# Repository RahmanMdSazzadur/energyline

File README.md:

# EnergyLine

Assembly-line simulation, a virtual fastening cell, n8n workflows, a routed PCB prototype and a standalone Arduino demonstration.

Start with `START_HERE.md` or open `RELEASE_INDEX.html` from the extracted folder. Version 1.1.1 combines all current deliverables in `EnergyLine-v1.1.1-final.zip`.

EnergyLine studies how a five-station mock energy-module assembly line could meet a demand of 240 good units per shift. The model compares staffing, finite buffers, a second manual fixture and selective automation. Process times, failure rates, quality inputs and prices are assumptions. No physical production data is used.

## Access and reuse

- Run the full Python app online: https://energyline-demo.onrender.com/
- Public repository: https://github.com/RahmanMdSazzadur/energyline
- Online project overview: https://rahmanmdsazzadur.github.io/energyline/
- Download the reviewed package: https://github.com/RahmanMdSazzadur/energyline/releases/tag/v1.1.1
- Interactive Arduino demonstration: https://wokwi.com/projects/480261288480719873

The project page serves static documentation, video, drawings and saved circuit results. It does not run the Python app or n8n in the browser. To run the full app, clone this repository, enter its folder, and follow the local setup below. GitHub Actions checks the software tests, Arduino controller core and archive contents; it does not run physical hardware tests.

```sh
git clone https://github.com/RahmanMdSazzadur/energyline.git
cd energyline
python3 src/api/server.py
```

The full Python app is live on Render Free at https://energyline-demo.onrender.com/. Visitors do not need an account or local Python setup. Free hosting sleeps when idle and stores shared, temporary runs. `render.yaml` and `docs/hosting.md` describe deployment and limits. The tagged v1.1.1 ZIP is the reviewed local-prototype release; the main branch also includes the hosted-demo additions.

Original project work is available under the MIT license. See `LICENSE`, `THIRD_PARTY_NOTICES.md` and `CONTRIBUTING.md`.

## Main result

With the faster S2/S3 configuration, four production operators plus one rework operator meet demand in 198 of 200 simulated shifts. The 95% Wilson lower bound is 96.4%. Three production operators cost less per unit but meet demand in 183 of 200 shifts, with an 86.8% lower bound.

Adding a second manual S3 resource at fixed staffing raises output from 163.4 to 200.5 units per shift. S2 then limits the line. The study therefore supports investigating both S2 and S3 rather than buying an S3 machine on the basis of its standalone cycle time.

These results apply to the configured model. Loading, walking, unloading and inspection performance need measured inputs before an equipment decision.

## Run locally

Use Python 3.13.7. The application and tests use the standard library; no pip packages are required.

`python3 src/api/server.py`

Open `http://localhost:8787/portfolio` for the case study, drawings and video. The application also provides the experiment studio at `/`, the S3 cell at `/cell` and the cost comparison at `/costs`. These are local addresses, not public hosting links.

For Docker and n8n setup, see `n8n/README.md`. n8n coordinates experiments and commissioning tests; it does not control physical motion.

## Verify and reproduce

- Tests: `python3 -m unittest discover -s tests -q`
- Regenerate numerical evidence and drawings: `python3 scripts/reproduce.py`
- Optional video rendering: `python3 scripts/build_demo.py` (requires `requirements-media.txt` and ffmpeg).
- Build the source archive: `python3 scripts/package_release.py`

The reviewed version has 103 passing tests and 11 recorded commissioning cases. Six cost configurations each use 200 replications. Separate studies cover staffing, timing variation, failures, quality, parallel S3 resources and the per-unit controller adapter. Seeds, configurations and checksums are saved with the results.

## Project structure

- `src/simulation/`: production flow, operators, buffers, quality and reliability.
- `src/controls/`, `src/equipment_model/`, `src/cell/`: S3 controller, plant and commissioning harness.
- `src/analysis/`: experiment drivers and conversion-cost calculations.
- `configs/`: model and cost inputs.
- `tests/`: reference cases, invariants, fault responses and API checks.
- `cad/`: OpenSCAD concepts, dimensioned SVG drawings and a DXF layout.
- `docs/final_case_study.md`: methods, results and engineering interpretation.
- `docs/engineering_review.md`: review findings and corrections.
- `docs/assumptions_register.md`, `docs/requirements_audit.csv`: input and evidence records.
- `n8n/`: workflow definitions and setup instructions.
- `media/`: two-minute software demonstration and captions.
- `electrical/`: KiCad project, routed Revision A PCB, 3D envelope, ngspice evidence and fabrication files.
- `wokwi/`: Arduino sketch, virtual wiring, tests and saved project URL.
- `docs/release_notes.md`: combined release contents and component boundaries.

## Limits

The cell and line adapter run in software. Cell timings are scaled to an assumed line cycle, and the adapter resets the cell each cycle. Its results are reported separately from the economic study.

Mechanical CAD is conceptual and has not been compiled or qualified for manufacture. The electrical PCB has passed configured KiCad DRC, ERC and schematic parity checks, but has not been manufactured or physically tested. The Wokwi LED controller is a standalone demonstration, not a full port of the virtual S3 controller or a connection to n8n. No measured assembly times, real machine operation, supplier quotations or certified safety functions are claimed. The model omits separate walking/unloading tasks, inspection errors, constrained repair labor, replenishment and shift carryover. Good-unit materials and general overhead are excluded from the reported conversion cost.

Version 1.1.1 is a combined simulation and engineering-prototype release. PCB Revision A and the Wokwi demonstration retain their own validation limits; see `docs/scope_and_validation.md`.

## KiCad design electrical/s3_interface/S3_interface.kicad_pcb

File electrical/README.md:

# S3 bench interface and simulation

This extension models a 5 V bench interface with an LED mock clamp load and two active-low dry-contact inputs. It is not an industrial actuator circuit or a certified safety circuit.

## Open and reproduce

Start the browser KiCad service with `docker compose -f electrical/compose.yaml up -d`, then open http://localhost:3090. The project inside KiCad is `/project/S3_interface.kicad_pro`.

Export the schematic connectivity before rerunning a changed design:

```sh
docker exec energyline-kicad kicad-cli sch export netlist --format kicadxml --output /project/S3_interface.net.xml /project/S3_interface.kicad_sch
docker exec energyline-kicad apk add --no-cache ngspice
python3 electrical/run_simulation.py
```

The ngspice installation is local to the container and must be repeated if it is recreated. The runner checks the exported net connections, derives component values from that export, and adds explicit simulation sources and generic device models. It runs ngspice externally rather than through KiCad's integrated simulator.

## Results

The 40 ms transient run produced 20,201 samples and passed 12 functional checks. Enabled LED current was 4.149 mA, transistor collector voltage was 0.049 V, and input 10–90% rise time was 219.83 microseconds. Removing the permit inhibited LED current while the command remained high.

Open `s3_interface/simulation/report.html`, or http://localhost:8787/circuit-simulation while the main application is running. Raw results, the SPICE deck, engine log, CSV samples and SVG waveforms are in `s3_interface/simulation/`.

## Model limits

The NPN and LED models are generic; the BC547B is not calibrated against manufacturer measurements. Controller outputs and contacts are ideal sources/switches. The fuse is represented by 1 ohm and does not trip. Input thresholds of 1.5/3.5 V are assumed. Mechanical bounce, EMC, ESD, tolerance and thermal effects are not analyzed. The 100 microsecond RC time constant is not a complete mechanical debounce solution. These results demonstrate modeled behavior, not tested hardware performance.

The combined EnergyLine v1.1.0 release includes this electrical extension alongside the software and Wokwi files.

## Routed PCB Revision A

The current board is `s3_interface/S3_interface.kicad_pcb`, with assembly details in `s3_interface/ASSEMBLY.md`. It uses standard library footprints, four M3 mounting holes and complete two-layer routing. DRC, schematic parity and ERC reports are saved alongside it. Fabrication exports are in `s3_interface/fabrication/rev_A/`. The superseded placement draft is excluded from the combined release.

To regenerate after confirming component choices, copy `electrical/pcb_components.json` to `electrical/s3_interface/pcb_components.json`, regenerate the schematic and XML netlist, then run `docker exec energyline-kicad python3 /project/build_rev_a.py`. Rerun DRC, ERC and simulation after any design change, and regenerate manufacturing files from the checked board. Native KiCad footprints are taken from the installed KiCad 10.0.3 library.

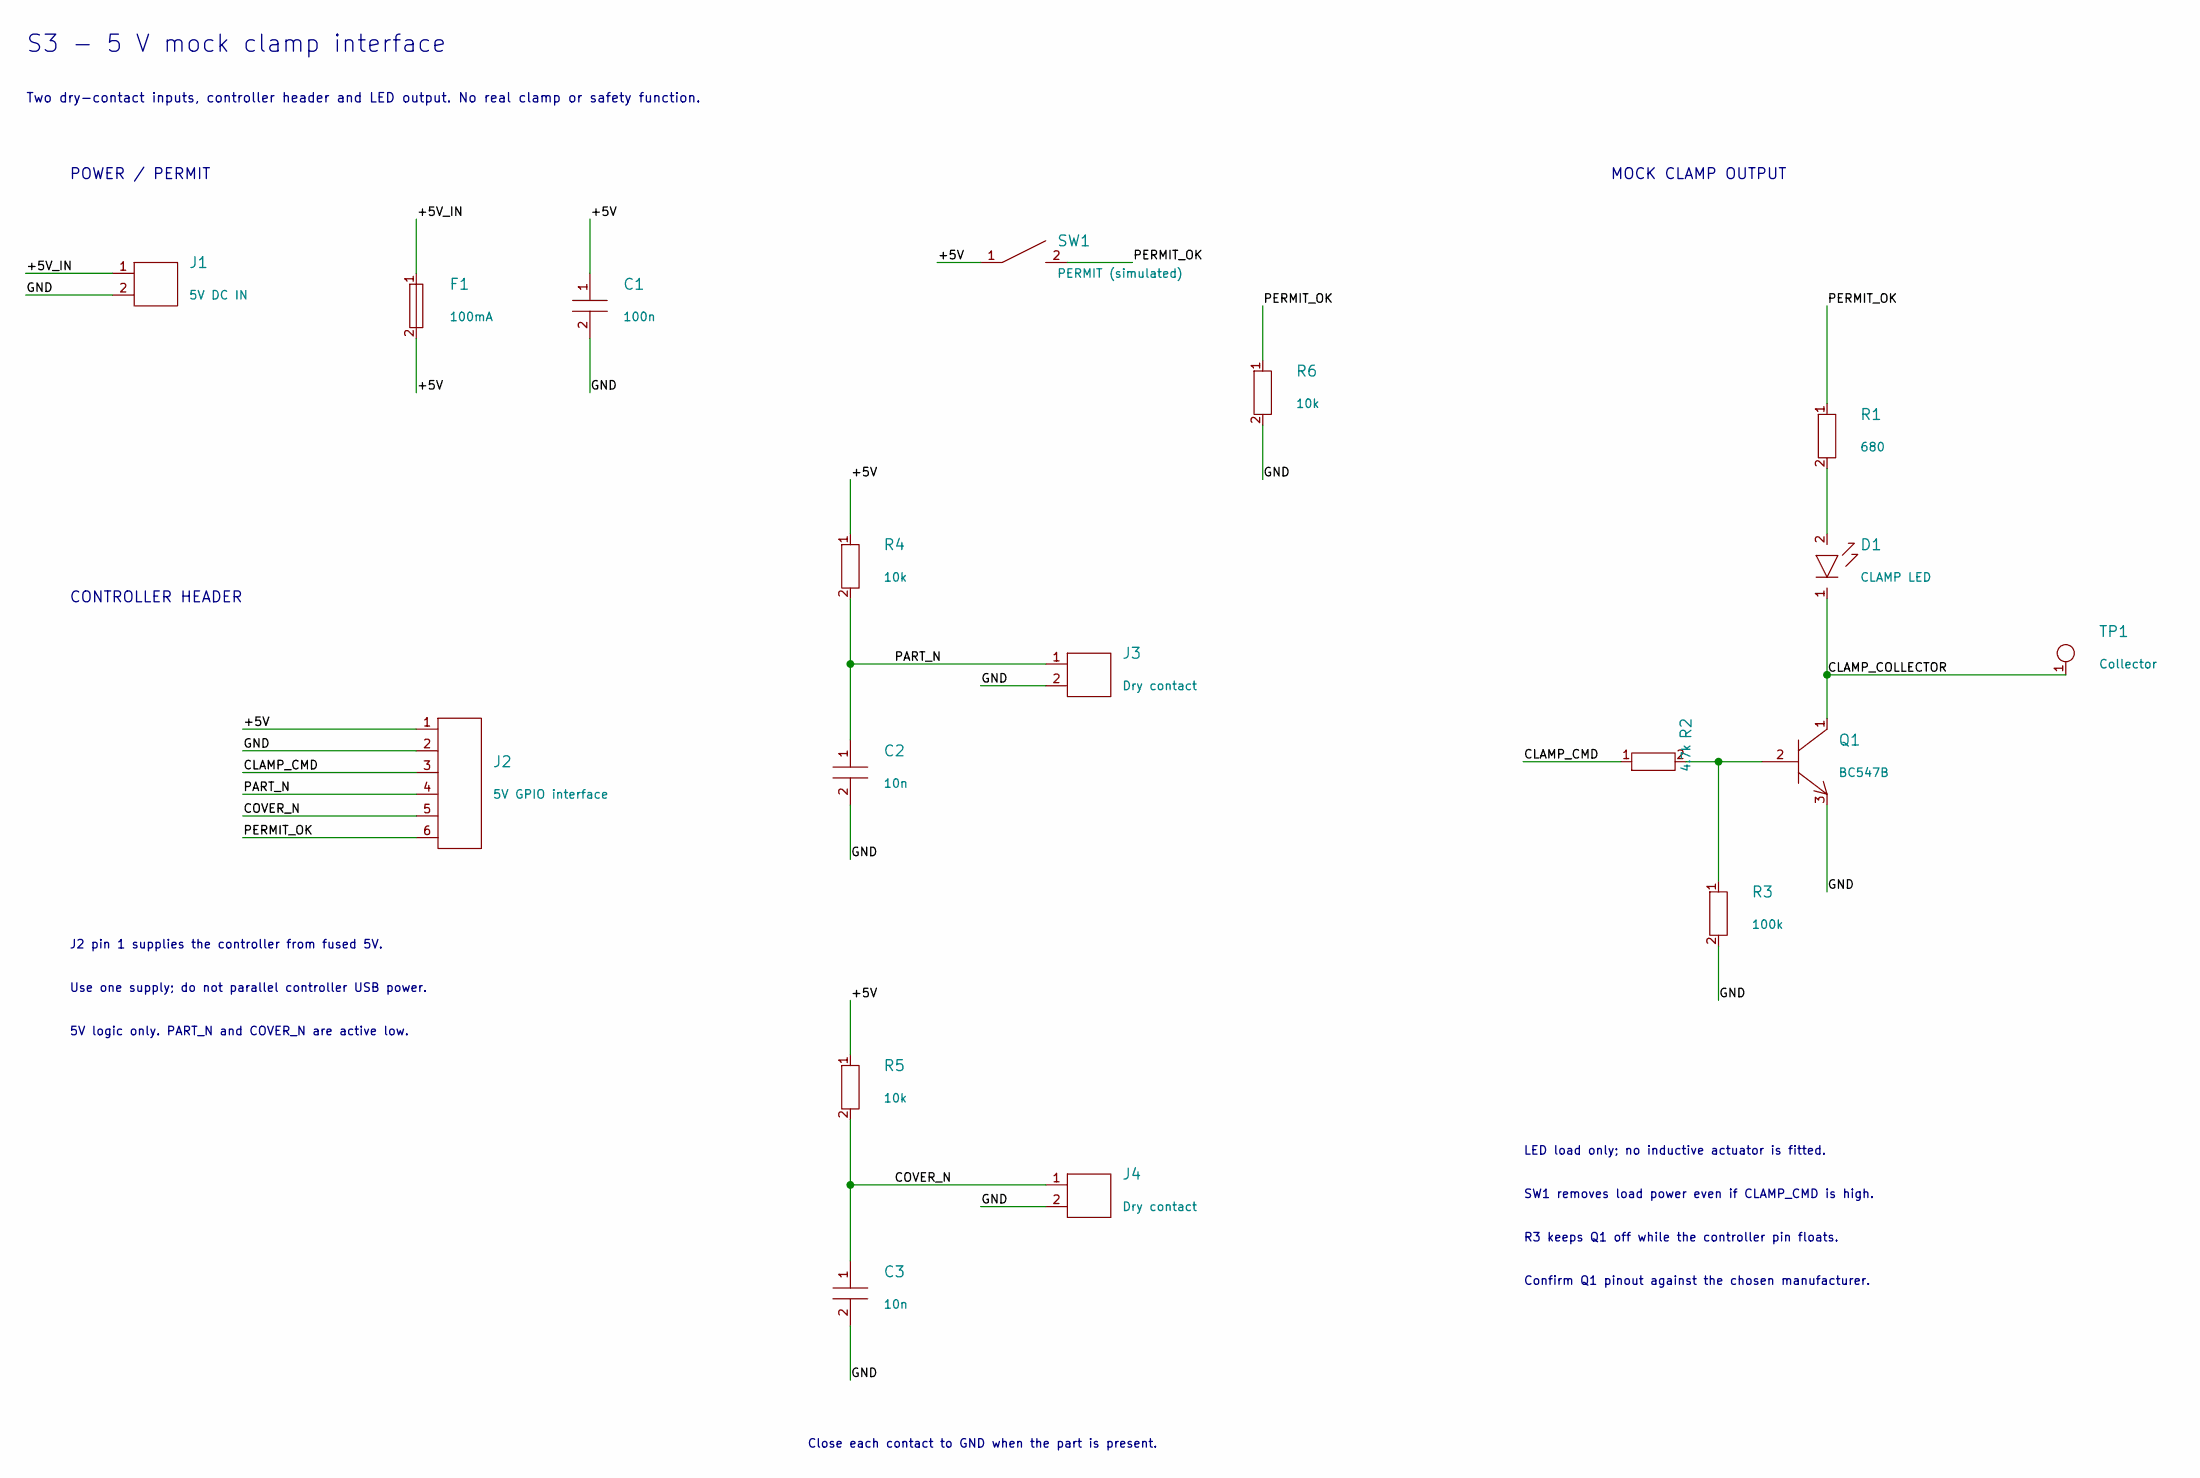
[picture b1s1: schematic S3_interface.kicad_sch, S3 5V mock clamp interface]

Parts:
C1: 100n; C_Disc_D5.0mm_W2.5mm_P5.00mm
C2, C3: 10n; C_Disc_D5.0mm_W2.5mm_P5.00mm
D1: CLAMP LED; LED_D3.0mm
F1: 100mA; Fuse_Littelfuse_372_D8.50mm
J1: 5V DC IN; PinHeader_1x02_P2.54mm_Vertical
J2: 5V GPIO interface; PinHeader_1x06_P2.54mm_Vertical
J3, J4: Dry contact; PinHeader_1x02_P2.54mm_Vertical
Q1: BC547B; TO-92_Inline_Wide
R1: 680; R_Axial_DIN0207_L6.3mm_D2.5mm_P7.62mm_Horizontal
R2: 4.7k; R_Axial_DIN0207_L6.3mm_D2.5mm_P7.62mm_Horizontal
R3: 100k; R_Axial_DIN0207_L6.3mm_D2.5mm_P7.62mm_Horizontal
R4, R5, R6: 10k; R_Axial_DIN0207_L6.3mm_D2.5mm_P7.62mm_Horizontal
SW1: PERMIT (simulated); PinHeader_1x02_P2.54mm_Vertical
TP1: Collector; TestPoint_THTPad_D2.0mm_Drill1.0mm

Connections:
/+5V: C1.1, F1.2, J2.1, R4.1, R5.1, SW1.1
/+5V_IN: F1.1, J1.1
/CLAMP_CMD: J2.3, R2.1
/CLAMP_COLLECTOR: D1.1 (K), Q1.1 (C), TP1.1
/COVER_N: C3.1, J2.5, J4.1, R5.2
/GND: C1.2, C2.2, C3.2, J1.2, J2.2, J3.2, J4.2, Q1.3 (E), R3.2, R6.2
/PART_N: C2.1, J2.4, J3.1, R4.2
/PERMIT_OK: J2.6, R1.1, R6.1, SW1.2
unnamed: D1.2 (A), R1.2
unnamed: Q1.2 (B), R2.2, R3.1

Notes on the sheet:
S3 - 5 V mock clamp interface
Two dry-contact inputs, controller header and LED output. No real clamp or safety function.
POWER / PERMIT
CONTROLLER HEADER
J2 pin 1 supplies the controller from fused 5V.
Use one supply; do not parallel controller USB power.
5V logic only. PART_N and COVER_N are active low.
Close each contact to GND when the part is present.
MOCK CLAMP OUTPUT
LED load only; no inductive actuator is fitted.
SW1 removes load power even if CLAMP_CMD is high.
R3 keeps Q1 off while the controller pin floats.
Confirm Q1 pinout against the chosen manufacturer.

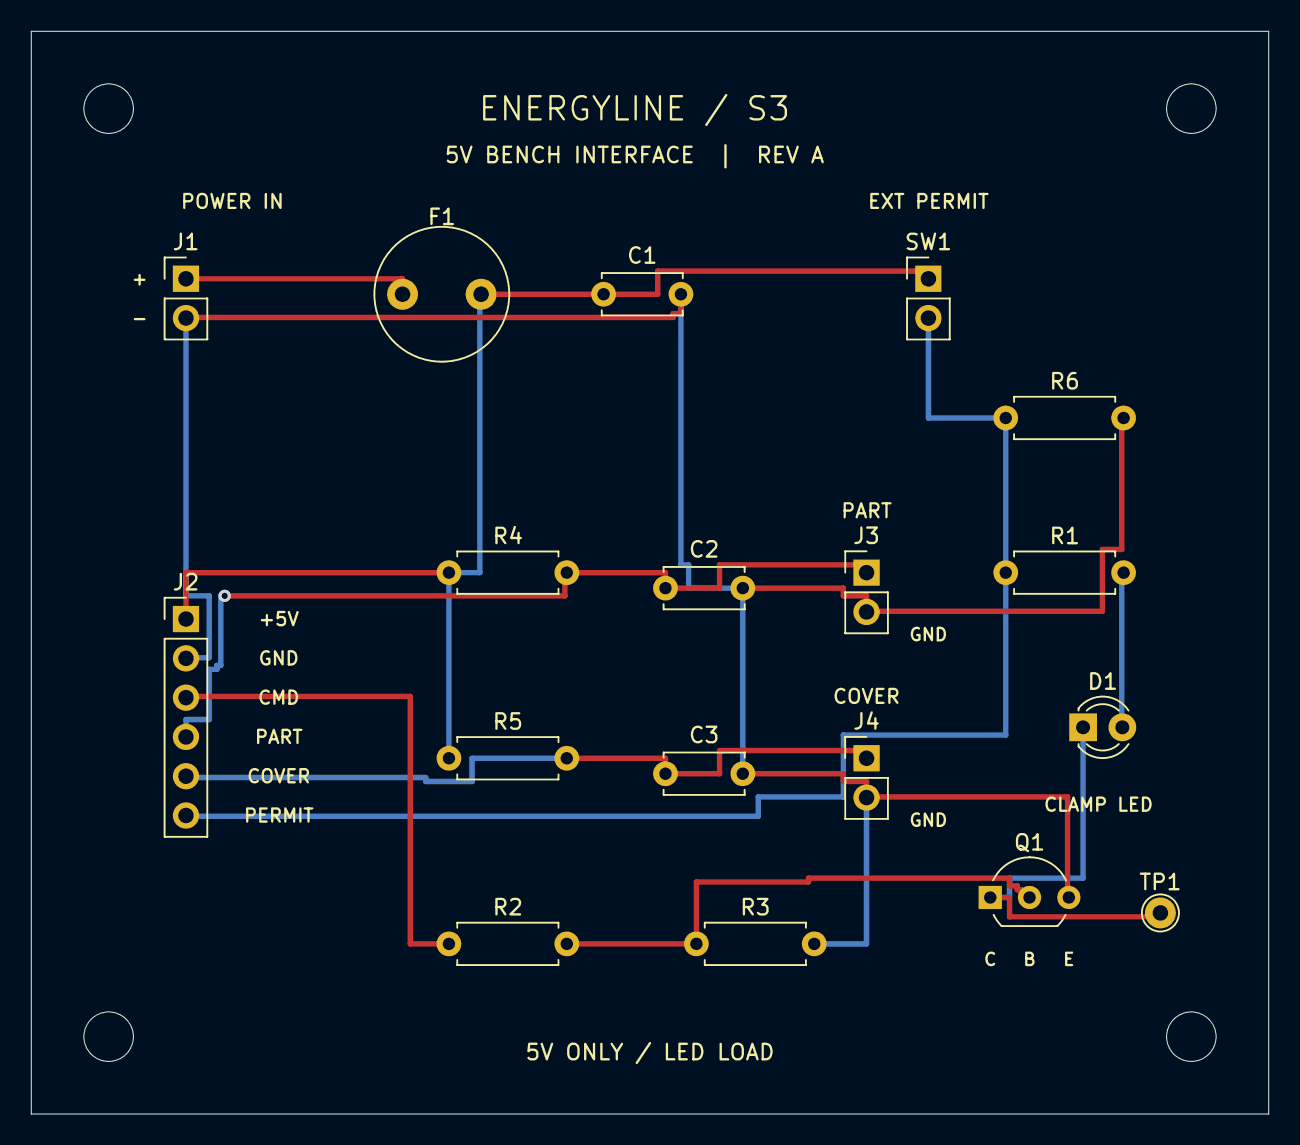
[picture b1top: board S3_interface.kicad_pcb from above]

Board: 2 copper layers, 80.0 x 70.0 mm, 22 parts (0 on the bottom side), 10 nets.

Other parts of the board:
H1, H2, H3, H4: M3; MountingHole_3.2mm_M3

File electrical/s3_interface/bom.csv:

reference,value,symbol,x_mm,y_mm,angle
J1,5V DC IN,Conn_2,30.48,43.18,0
F1,100mA,Fuse,60.96,45.72,0
C1,100n,C,81.28,45.72,0
SW1,PERMIT (simulated),Switch_SPST,132.08,40.64,0
R6,10k,R,160.02,55.88,0
J2,5V GPIO interface,Conn_6,66.04,101.6,0
R4,10k,R,111.76,76.2,0
J3,Dry contact,Conn_2,139.7,88.9,0
C2,10n,C,111.76,100.33,0
R5,10k,R,111.76,137.16,0
J4,Dry contact,Conn_2,139.7,149.86,0
C3,10n,C,111.76,161.29,0
R1,680,R,226.06,60.96,0
D1,CLAMP LED,LED,226.06,76.2,0
Q1,BC547B,NPN_CBE,223.52,99.06,0
R2,4.7k,R,205.74,99.06,90
R3,100k,R,213.36,116.84,0
TP1,Collector,TestPoint,254,86.36,0

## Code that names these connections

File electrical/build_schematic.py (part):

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
    d.text('CONTROLLER HEADER',20.32,80.01)
    j2=d.place('Conn_6','J2','5V GPIO interface',66.04,101.6)
    mapping=['+5V','GND','CLAMP_CMD','PART_N','COVER_N','PERMIT_OK']
    for number,name in enumerate(mapping,1):d.stub(j2[str(number)],(40.64,j2[str(number)][1]),name)
    d.text('J2 pin 1 supplies the controller from fused 5V.',20.32,120.65,1.0)
    d.text('Use one supply; do not parallel controller USB power.',20.32,125.73,1.0)
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    d.stub(r1['1'],(226.06,45.72),'PERMIT_OK')
    led=d.place('LED','D1','CLAMP LED',226.06,76.2);d.wire(r1['2'],led['2'])
    transistor=d.place('NPN_CBE','Q1','BC547B',223.52,99.06);d.wire(led['1'],transistor['1'])
    d.label('CLAMP_COLLECTOR',(226.06,88.9))
    r2=d.place('R','R2','4.7k',205.74,99.06,90)
    d.stub(r2['1'],(190.5,99.06),'CLAMP_CMD');d.wire(r2['2'],transistor['2'])
    r3=d.place('R','R3','100k',213.36,116.84)
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    (OUT/'sym-lib-table').write_text('(sym_lib_table (version 7) (lib (name "EnergyLine") (type "KiCad") (uri "${KIPRJMOD}/EnergyLine.kicad_sym") (options "") (descr "S3 bench interface symbols")))\n')
    with (OUT/'bom.csv').open('w',newline='') as handle:
        writer=csv.DictWriter(handle,fieldnames=list(d.parts[0]));writer.writeheader();writer.writerows(d.parts)
    (OUT/'io_mapping.json').write_text(json.dumps({'controller_header':{str(i+1):net for i,net in enumerate(mapping)},'active_low_inputs':['PART_N','COVER_N'],'output_load':'LED only','supply_v':5,'safety_function':False},indent=2)+'\n')
    print('Created native KiCad project with',len(d.parts),'components.')


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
